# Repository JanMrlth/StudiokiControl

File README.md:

# Studioki Controll

## Overview
The Studioki Controller is a temperatur controller for kilns. It uses an ESP32 to controll its functions. Because it is build with one specific oven in mind, we use its temperature probe. (https://laborofen.com/de/Steuerungen/Thermoelemente/Thermoelement-NiCr-Ni7) These thermocouples are used in a wide variety of ovens. 

## Structure of the project
This project consists of
* Schematics and PCB in KiCAD
* Hardware in Fusion360 - published as steps
* Software in Python

https://github.com/espressif/esptool/wiki/ESP32-Boot-Mode-Selection

https://github.com/apollo-ng/picoReflow

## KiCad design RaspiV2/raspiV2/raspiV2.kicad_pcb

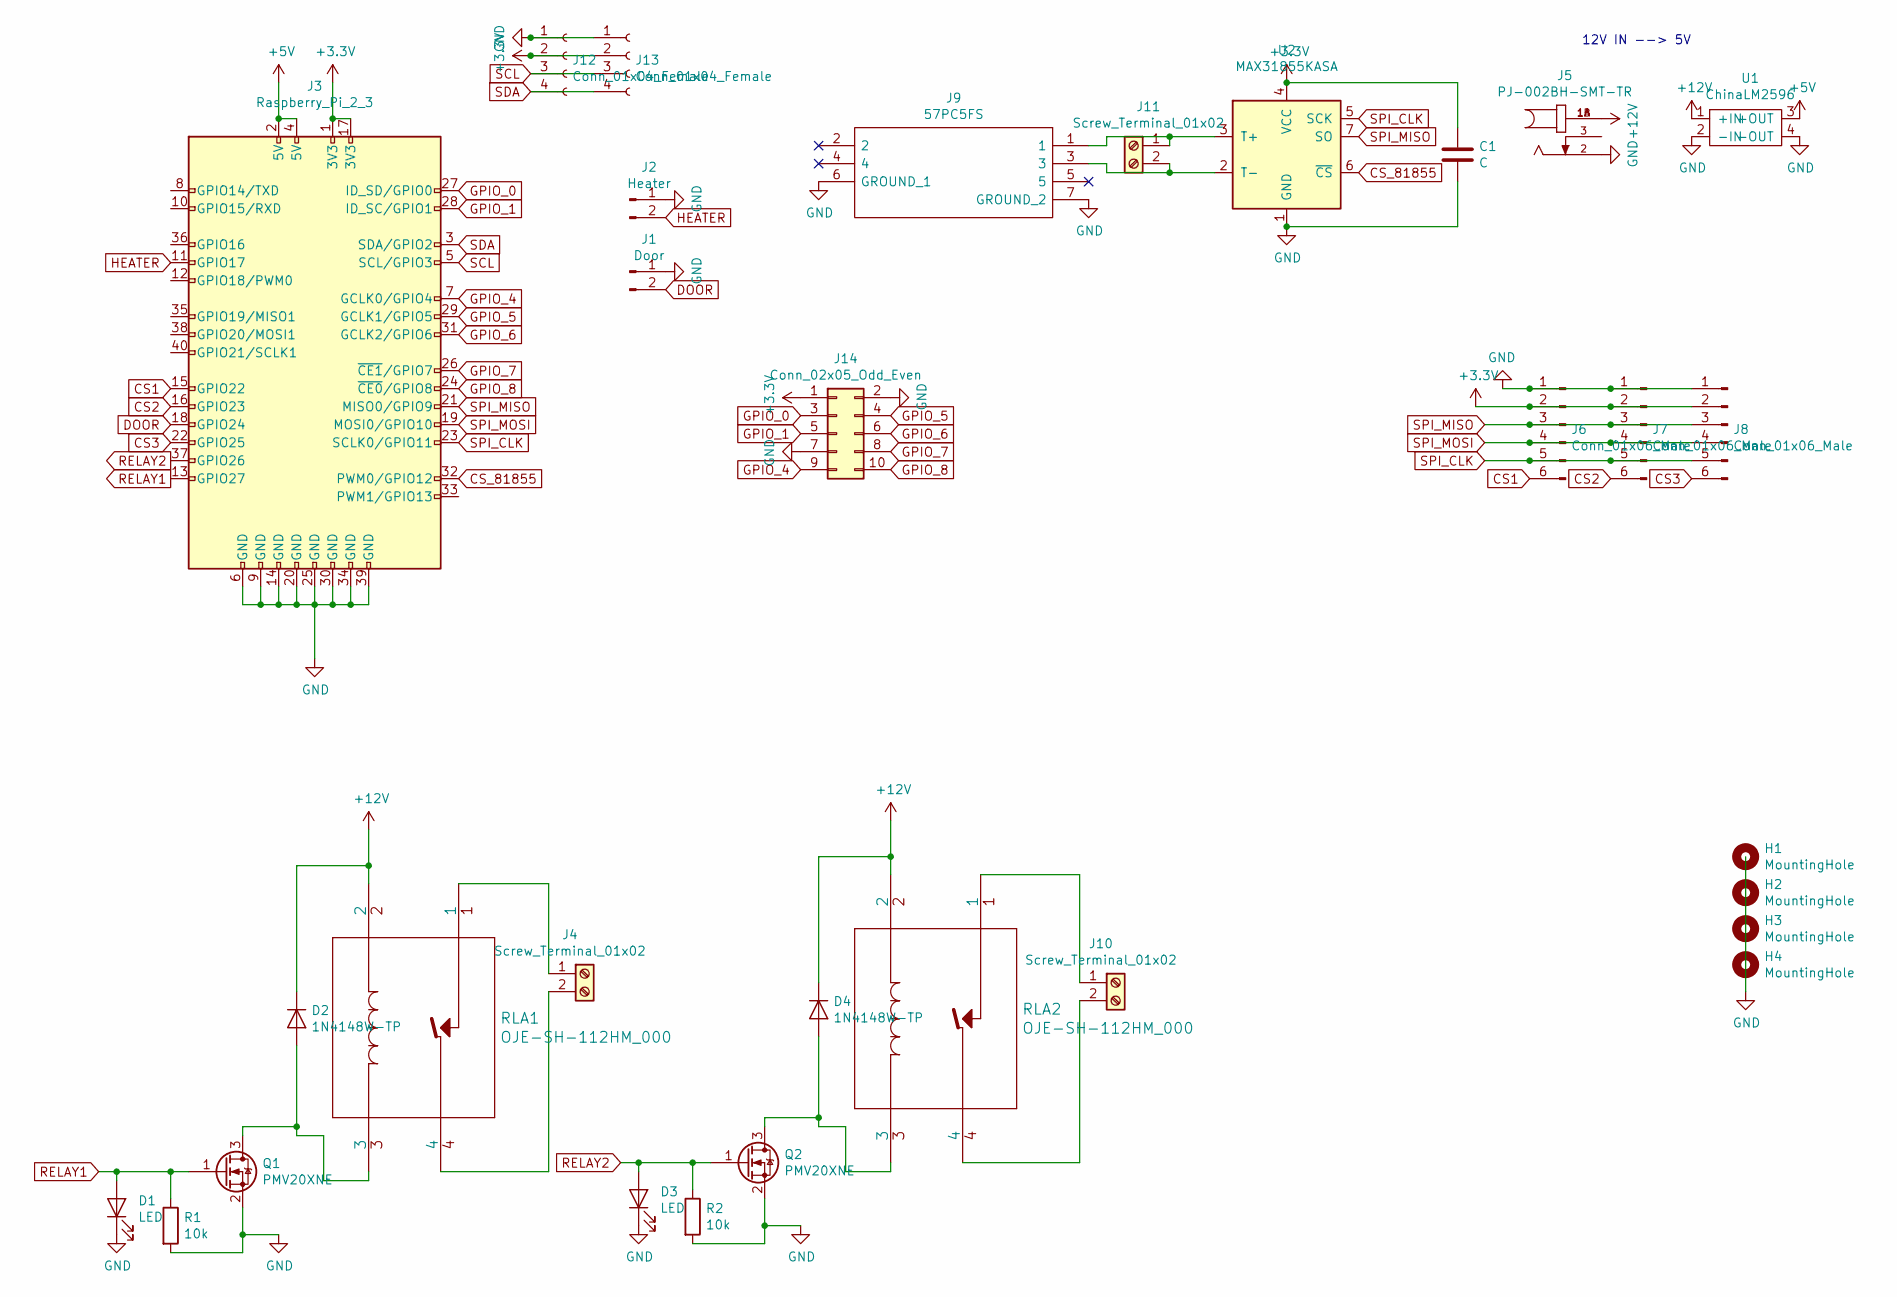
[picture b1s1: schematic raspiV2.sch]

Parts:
C1: C; C_0603_1608Metric
D1, D3: LED; LED_0603_1608Metric
D2, D4: 1N4148W-TP; D_SOD-123
H1, H2, H3, H4: MountingHole; MountingHole_2.7mm_M2.5_ISO7380_Pad
J1: Door; TerminalBlock_Phoenix_PT-1,5-2-5.0-H_1x02_P5.00mm_Horizontal
J2: Heater; TerminalBlock_Phoenix_PT-1,5-2-5.0-H_1x02_P5.00mm_Horizontal
J3: Raspberry_Pi_2_3; PinHeader_2x20_P2.54mm_Vertical
J4, J10, J11: Screw_Terminal_01x02; TerminalBlock_Phoenix_PT-1,5-2-5.0-H_1x02_P5.00mm_Horizontal
J5: PJ-002BH-SMT-TR; CUI_PJ-002BH-SMT-TR
J6, J7, J8: Conn_01x06_Male; PinHeader_1x06_P2.54mm_Vertical
J9: 57PC5FS; Mouser Part Number 502-57PC5FS
J12, J13: Conn_01x04_Female; PinSocket_1x04_P2.54mm_Vertical
J14: Conn_02x05_Odd_Even; IDC-Header_2x05_P2.54mm_Vertical
Q1, Q2: PMV20XNE; SOT-23
R1, R2: 10k; R_0603_1608Metric
RLA1, RLA2: OJE-SH-112HM_000
U1: ChinaLM2596; LM2596-Chinamodule
U2: MAX31855KASA; SOIC-8_3.9x4.9mm_P1.27mm

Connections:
+3V3: C1.1, J3.1 (3V3), J3.17 (3V3), J6.2, J7.2, J8.2, J12.2, J13.2, J14.1, U2.4 (VCC)
+5V: J3.2 (5V), J3.4 (5V), U1.3 (+OUT)
+12V: D2.1 (K), D4.1 (K), J5.1A (1), J5.1B (1), RLA1.2, RLA2.2, U1.1 (+IN)
CS1: J3.15 (GPIO22), J6.6
CS2: J3.16 (GPIO23), J7.6
CS3: J3.22 (GPIO25), J8.6
CS_81855: J3.32 (PWM0/GPIO12), U2.6 (~CS~)
DOOR: J1.2, J3.18 (GPIO24)
GND: C1.2, D1.1 (K), D3.1 (K), J1.1, J2.1, J3.6 (GND), J3.9 (GND), J3.14 (GND), J3.20 (GND), J3.25 (GND), J3.30 (GND), J3.34 (GND), J3.39 (GND), J5.2, J6.1, J7.1, J8.1, J9.6 (GROUND_1), J9.7 (GROUND_2), J12.1, J13.1, J14.2, J14.7, Q1.2 (S), Q2.2 (S), R1.2, R2.2, U1.2 (-IN), U1.4 (-OUT), U2.1 (GND)
GPIO_0: J3.27 (ID_SD/GPIO0), J14.3
GPIO_1: J3.28 (ID_SC/GPIO1), J14.5
GPIO_4: J3.7 (GCLK0/GPIO4), J14.9
GPIO_5: J3.29 (GCLK1/GPIO5), J14.4
GPIO_6: J3.31 (GCLK2/GPIO6), J14.6
GPIO_7: J3.26 (~CE1~/GPIO7), J14.8
GPIO_8: J3.24 (~CE0~/GPIO8), J14.10
HEATER: J2.2, J3.11 (GPIO17)
unnamed: D2.2 (A), Q1.3 (D), RLA1.3
unnamed: D4.2 (A), Q2.3 (D), RLA2.3
unnamed: J4.1, RLA1.1
unnamed: J4.2, RLA1.4
unnamed: J10.1, RLA2.1
unnamed: J10.2, RLA2.4
unnamed: J9.1, J11.1, U2.3 (T+)
unnamed: J9.3, J11.2, U2.2 (T-)
RELAY1: D1.2 (A), J3.13 (GPIO27), Q1.1 (G), R1.1
RELAY2: D3.2 (A), J3.37 (GPIO26), Q2.1 (G), R2.1
SCL: J3.5 (SCL/GPIO3), J12.3, J13.3
SDA: J3.3 (SDA/GPIO2), J12.4, J13.4
SPI_CLK: J3.23 (SCLK0/GPIO11), J6.5, J7.5, J8.5, U2.5 (SCK)
SPI_MISO: J3.21 (MISO0/GPIO9), J6.3, J7.3, J8.3, U2.7 (SO)
SPI_MOSI: J3.19 (MOSI0/GPIO10), J6.4, J7.4, J8.4

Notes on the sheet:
12V IN --> 5V

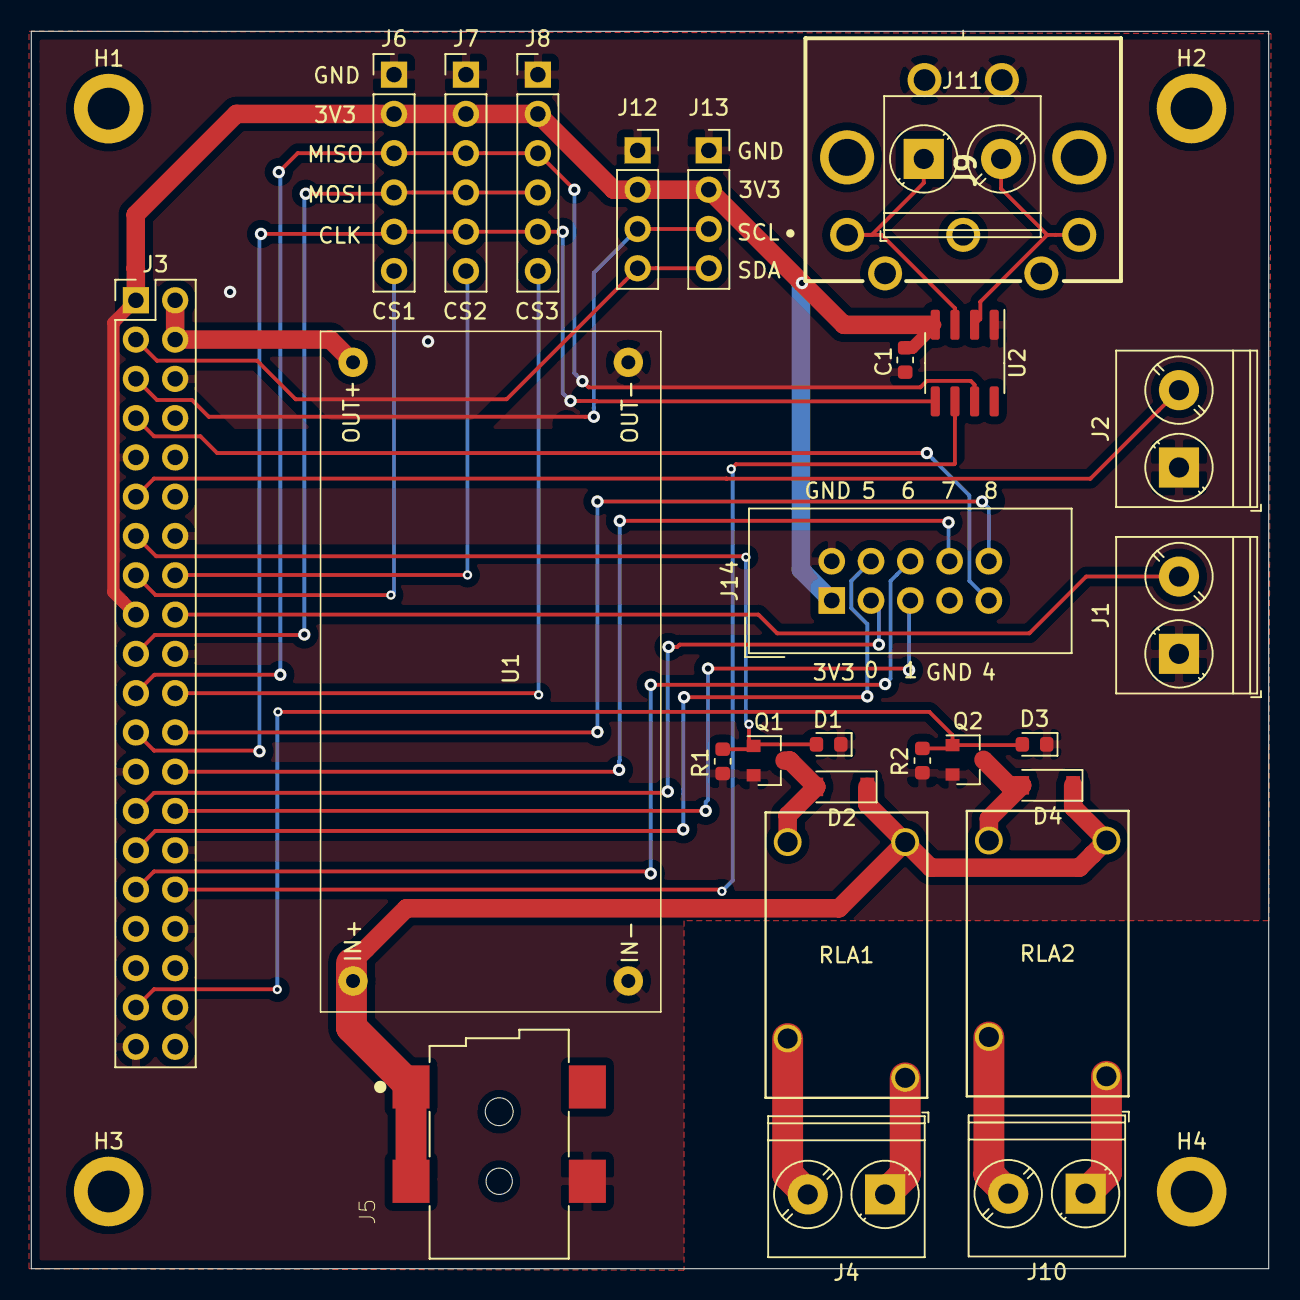
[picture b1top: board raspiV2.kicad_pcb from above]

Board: 2 copper layers, 80.0 x 80.0 mm, 31 parts (0 on the bottom side), 32 nets.

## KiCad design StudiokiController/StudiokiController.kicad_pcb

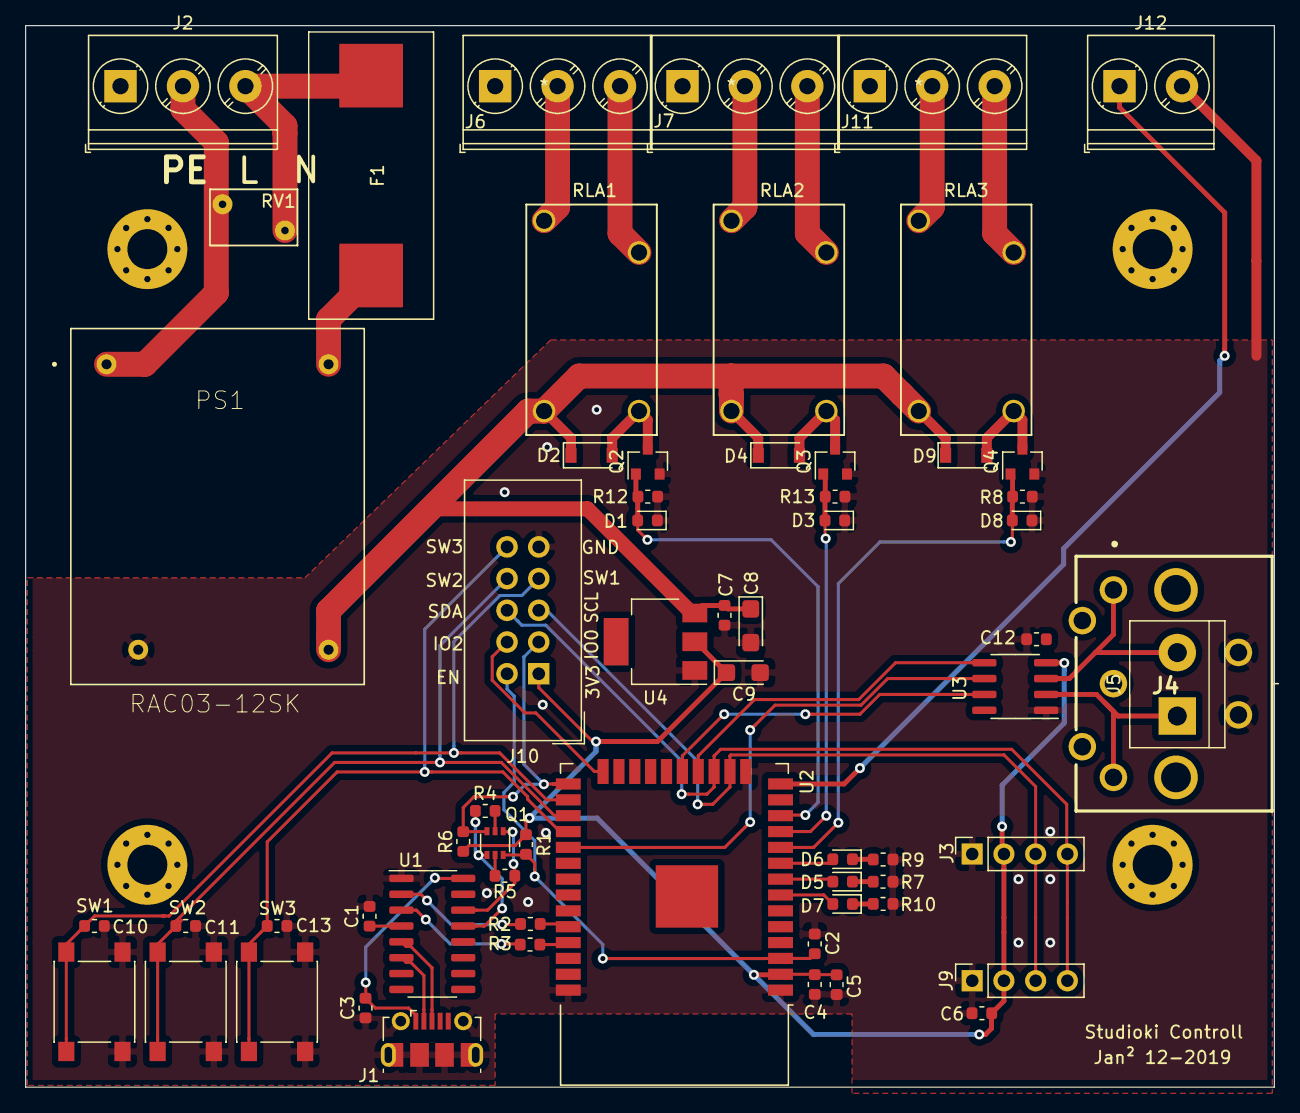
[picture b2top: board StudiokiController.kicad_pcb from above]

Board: 2 copper layers, 100.0 x 85.0 mm, 66 parts (0 on the bottom side), 49 nets.

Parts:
C1, C2, C4, C6, C7, C10, C11, C12, C13: 100nF; C_0603_1608Metric
C3: 1uF; C_0603_1608Metric
C5: 22uF; C_0603_1608Metric
C8, C9: 10uF tantal; CP_EIA-3216-12_Kemet-S
D1, D3, D5, D6, D7, D8: LED; LED_0603_1608Metric
D2, D4, D9: 1N4148W-TP; D_SOD-123
F1: Fuse; Littelfuse65800001009
H1, H2, H3, H4: MountingHole; MountingHole_3.2mm_M3_Pad_Via
J1: USB_B_Mini; USB_Micro-B_Molex-105017-0001
J2, J6, J7, J11: Screw_Terminal_01x03; TerminalBlock_Phoenix_PT-1,5-3-5.0-H_1x03_P5.00mm_Horizontal
J3, J9: Conn_01x04_Female; PinSocket_1x04_P2.54mm_Vertical
J4: 57PC5FS
J5: Conn_01x02_Female; TerminalBlock_bornier-2_P5.08mm
J10: Conn_01x10_Male; IDC-Header_2x05_P2.54mm_Vertical
J12: Screw_Terminal_01x02; TerminalBlock_Phoenix_PT-1,5-2-5.0-H_1x02_P5.00mm_Horizontal
PS1: RAC03-12SK; CONV_RAC03-12SK
Q1: Q_DUAL_NPN_NPN_E1B1C2E2B2C1; SOT-363_SC-70-6
Q2, Q3, Q4: PMV20XNE; SOT-23
R1, R4, R5, R6, R8, R12, R13: 10k; R_0603_1608Metric
R2, R3: 100R; R_0603_1608Metric
R7, R9, R10: 100; R_0603_1608Metric
RLA1, RLA2, RLA3: OJE-SH-112HM_000
RV1: MOV-07D391KTR; RV_Disc_D7mm_W4.5mm_P5mm
SW1, SW2, SW3: SW_Push; SW_SPST_PTS645
U1: CH340C; SOIC-16_3.9x9.9mm_P1.27mm
U2: ESP32-WROOM-32D; ESP32-WROOM-32
U3: MAX31855KASA; SOIC-8_3.9x4.9mm_P1.27mm
U4: AZ1117-3.3; SOT-223

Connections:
230V-L: J2.2, PS1.1, RV1.1
230V-N: F1.1, F1.2, J2.3, PS1.4, RV1.2
+3V3: C4.1, C5.1, C6.1, C9.1, C12.1, J3.2, J9.2, J10.1, R1.1, R6.2, U2.2, U3.4, U4.2
+12V: C7.1, C8.1, D2.1, D4.1, D9.1, PS1.3, RLA1.2, RLA2.2, RLA3.2, U4.3
/230V-Relay/OUTPUT-A: J6.3, RLA1.4
/230V-Relay/OUTPUT-B: J6.2, RLA1.1
/sheet5DF55D65/OUTPUT-A: J7.3, RLA2.4
/sheet5DF55D65/OUTPUT-B: J7.2, RLA2.1
/sheet5DF376A8/OUTPUT-A: J11.3, RLA3.4
/sheet5DF376A8/OUTPUT-B: J11.2, RLA3.1
CS_K1: U2.29, U3.6
DOOR: J12.1, U2.14
EN: C2.1, J10.2, Q1.6, R1.2, U2.3
GND: C1.2, C2.2, C3.1, C4.2, C5.2, C6.2, C7.2, C8.2, C9.2, C10.1, C11.1, C12.2, C13.1, D1.1, D3.1, D8.1, J1.5, J1.6, J3.1, J4.6, J4.7, J9.1, J10.9, J12.2, PS1.2, Q2.2, Q3.2, Q4.2, R7.1, R8.2, R9.1, R10.1, R12.2, R13.2, SW1.2, SW2.2, SW3.2, U1.1, U2.1, U2.15, U2.38, U3.1, U4.1
IO0: J10.3, Q1.3, R6.1, U2.25
IO2: J10.4, U2.24
LED1: D5.2, U2.8
LED2: D6.2, U2.9
LED3: D7.2, U2.7
unnamed: C1.1, U1.4
unnamed: C3.2, J1.1, U1.16
unnamed: D2.2, Q2.3, RLA1.3
unnamed: D4.2, Q3.3, RLA2.3
unnamed: D5.1, R7.2
unnamed: D6.1, R9.2
unnamed: D7.1, R10.2
unnamed: D9.2, Q4.3, RLA3.3
unnamed: J1.2, U1.6
unnamed: J1.3, U1.5
unnamed: J4.1, J5.2, U3.3
unnamed: J4.3, J5.1, U3.2
unnamed: Q1.1, R5.2, U1.14
unnamed: Q1.2, R4.1
unnamed: Q1.4, R4.2, U1.13
unnamed: Q1.5, R5.1
unnamed: R2.2, U1.2
unnamed: R3.2, U1.3
RELAY1: D1.2, Q2.1, R12.1, U2.12
RELAY2: D3.2, Q3.1, R13.1, U2.11
RELAY3: D8.2, Q4.1, R8.1, U2.10
SCL: J3.3, J9.3, J10.5, U2.16
SDA: J3.4, J9.4, J10.6, U2.17
SPI_MISO: U2.19, U3.7
SPI_SCK: U2.18, U3.5
SW1: C10.2, J10.7, SW1.1, U2.26
SW2: C11.2, J10.8, SW2.1, U2.27
SW3: C13.2, J10.10, SW3.1, U2.28
USB_RX: R3.1, U2.35
USB_TX: R2.1, U2.34

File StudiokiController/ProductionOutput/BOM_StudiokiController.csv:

ID;Bezeichner;Gehäuse;Stückzahl;Bezeichnung;Anbieter und Referenz
1;J1;USB_Micro-B_Molex-105017-0001;1;USB_B_Mini;
2;PS1;CONV_RAC03-12SK;1;RAC03-12SK;
3;J4;57PC5FS;1;57PC5FS;
4;J12;TerminalBlock_Phoenix_PT-1,5-2-5.0-H_1x02_P5.00mm_Horizontal;1;Screw_Terminal_01x02;
5;RV1;RV_Disc_D7mm_W4.5mm_P5mm;1;MOV-07D391KTR;
6;H1,H4,H3,H2;MountingHole_3.2mm_M3_Pad_Via;4;MountingHole;
7;J9,J8,J3;PinSocket_1x04_P2.54mm_Vertical;3;Conn_01x04_Female;
8;R10,R9,R7;R_0603_1608Metric;3;100R;
9;J10;IDC-Header_2x05_P2.54mm_Vertical;1;Conn_01x10_Male;
10;U1;SOIC-16_3.9x9.9mm_P1.27mm;1;CH340C;
11;RLA3,RLA1,RLA2;OJE-SH-112HM_000;3;OJE-SH-112HM_000;
12;R8,R4,R6,R1,R5,R12,R13;R_0603_1608Metric;7;10k;
13;C10,C12,C2,C4,C1,C6,C11,C7,C13;C_0603_1608Metric;9;100nF;
14;U2;ESP32-WROOM-32;1;ESP32-WROOM-32D;
15;SW3,SW2,SW1;SW_SPST_PTS645;3;SW_Push;
16;U4;SOT-223;1;AZ1117-3.3;
17;D8,D6,D5,D7,D3,D1;LED_0603_1608Metric;6;LED;
18;D9,D2,D4;D_SOD-123;3;1N4148W-TP;
19;Q4,Q3,Q2;SOT-23;3;PMV20XNE;
20;R3,R2;R_0603_1608Metric;2;100R;
21;J5;TerminalBlock_bornier-2_P5.08mm;1;Conn_01x02_Female;
22;Q1;SOT-363_SC-70-6;1;DMN2004DWK-7;
23;C3;C_0603_1608Metric;1;1uF;
24;C5;C_0603_1608Metric;1;22uF;
25;U3;SOIC-8_3.9x4.9mm_P1.27mm;1;MAX31855KASA;
26;C9,C8;CP_EIA-3216-12_Kemet-S;2;10uF tantal;
27;J6,J11,J7,J2;TerminalBlock_Phoenix_PT-1,5-3-5.0-H_1x03_P5.00mm_Horizontal;4;Screw_Terminal_01x03;
28;F1;Littelfuse65800001009;1;Fuse;

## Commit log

2019-12-05 Schematics: +ESP +OLED
2019-12-05 Added Datasheets
2019-12-05 Added MAX31855
2019-12-08 added several Parts
2019-12-08 first PCB
2019-12-08 changed silkscreen
2019-12-09 Bootmode
2019-12-11 New Layout
2019-12-11 deleted backups
2019-12-11 changed parameters
2019-12-14 new Tempsensor
2019-12-18 ProductionOutput
2020-02-21 New Project!
    New Project!
2020-02-23 gjkl
    fh
2020-02-24 minor changes

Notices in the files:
parts and their libraries:
Copyright 2016 Accelerated Designs. All rights reserved.
